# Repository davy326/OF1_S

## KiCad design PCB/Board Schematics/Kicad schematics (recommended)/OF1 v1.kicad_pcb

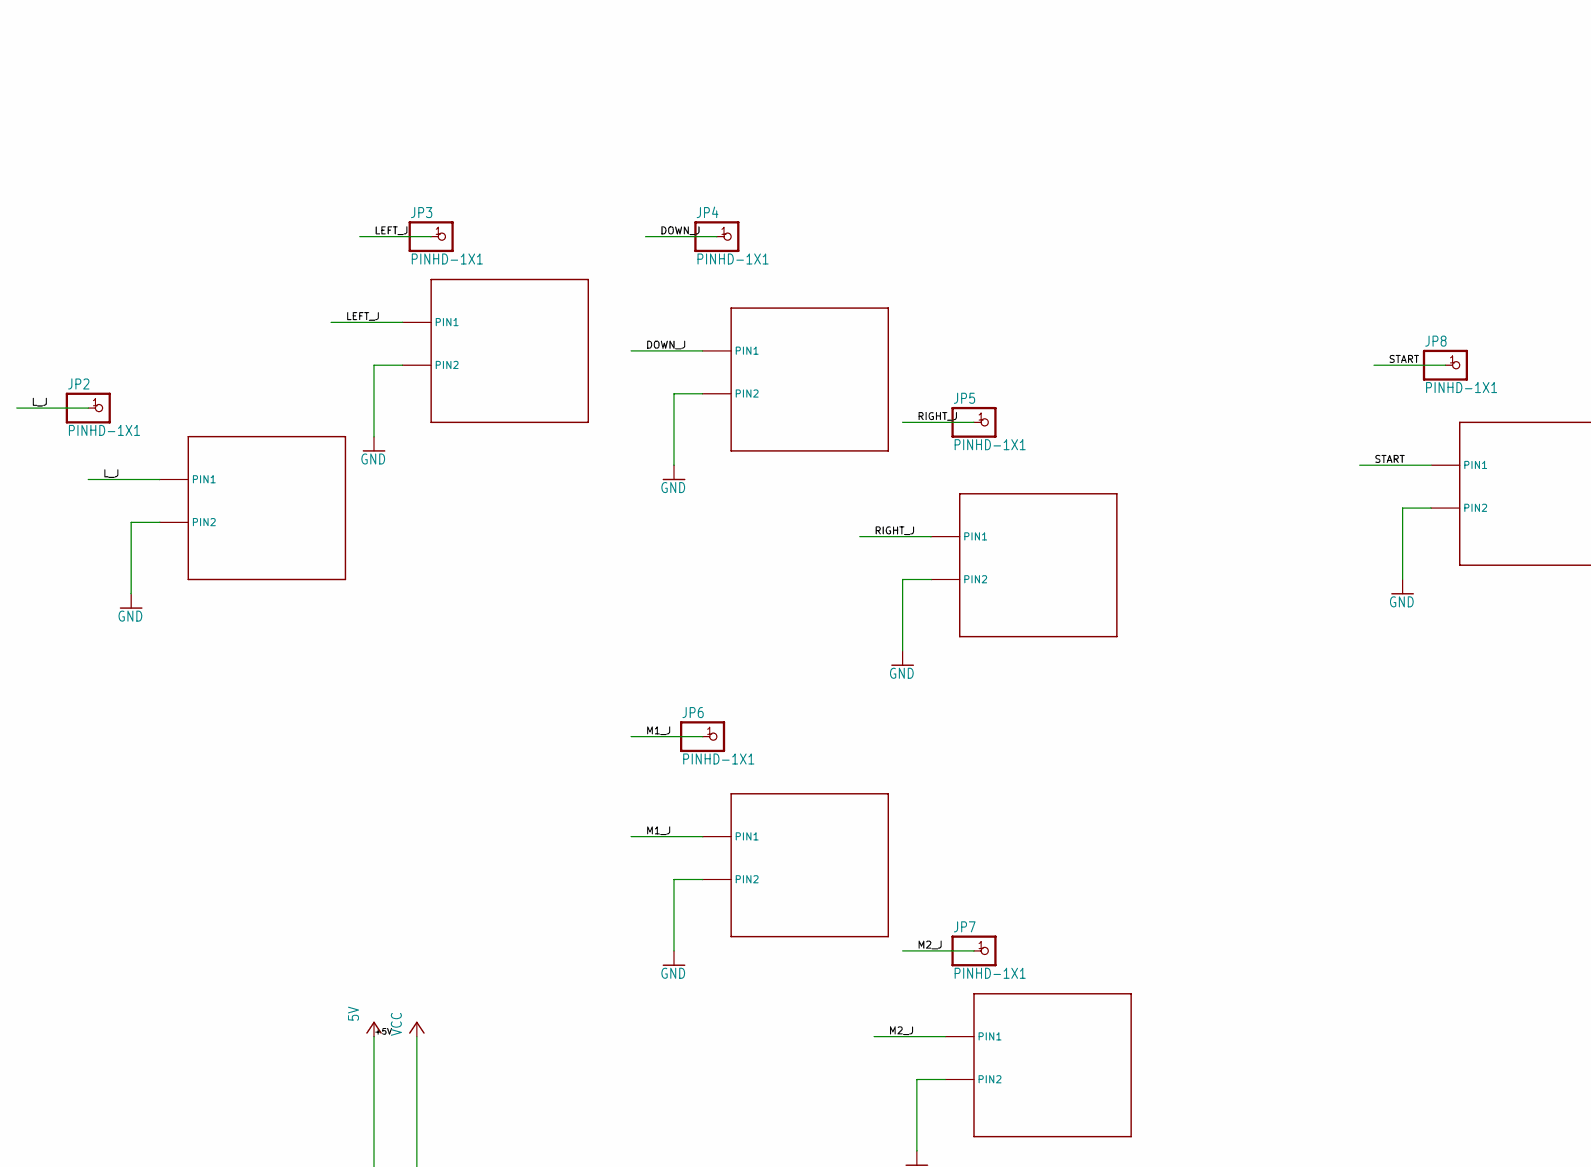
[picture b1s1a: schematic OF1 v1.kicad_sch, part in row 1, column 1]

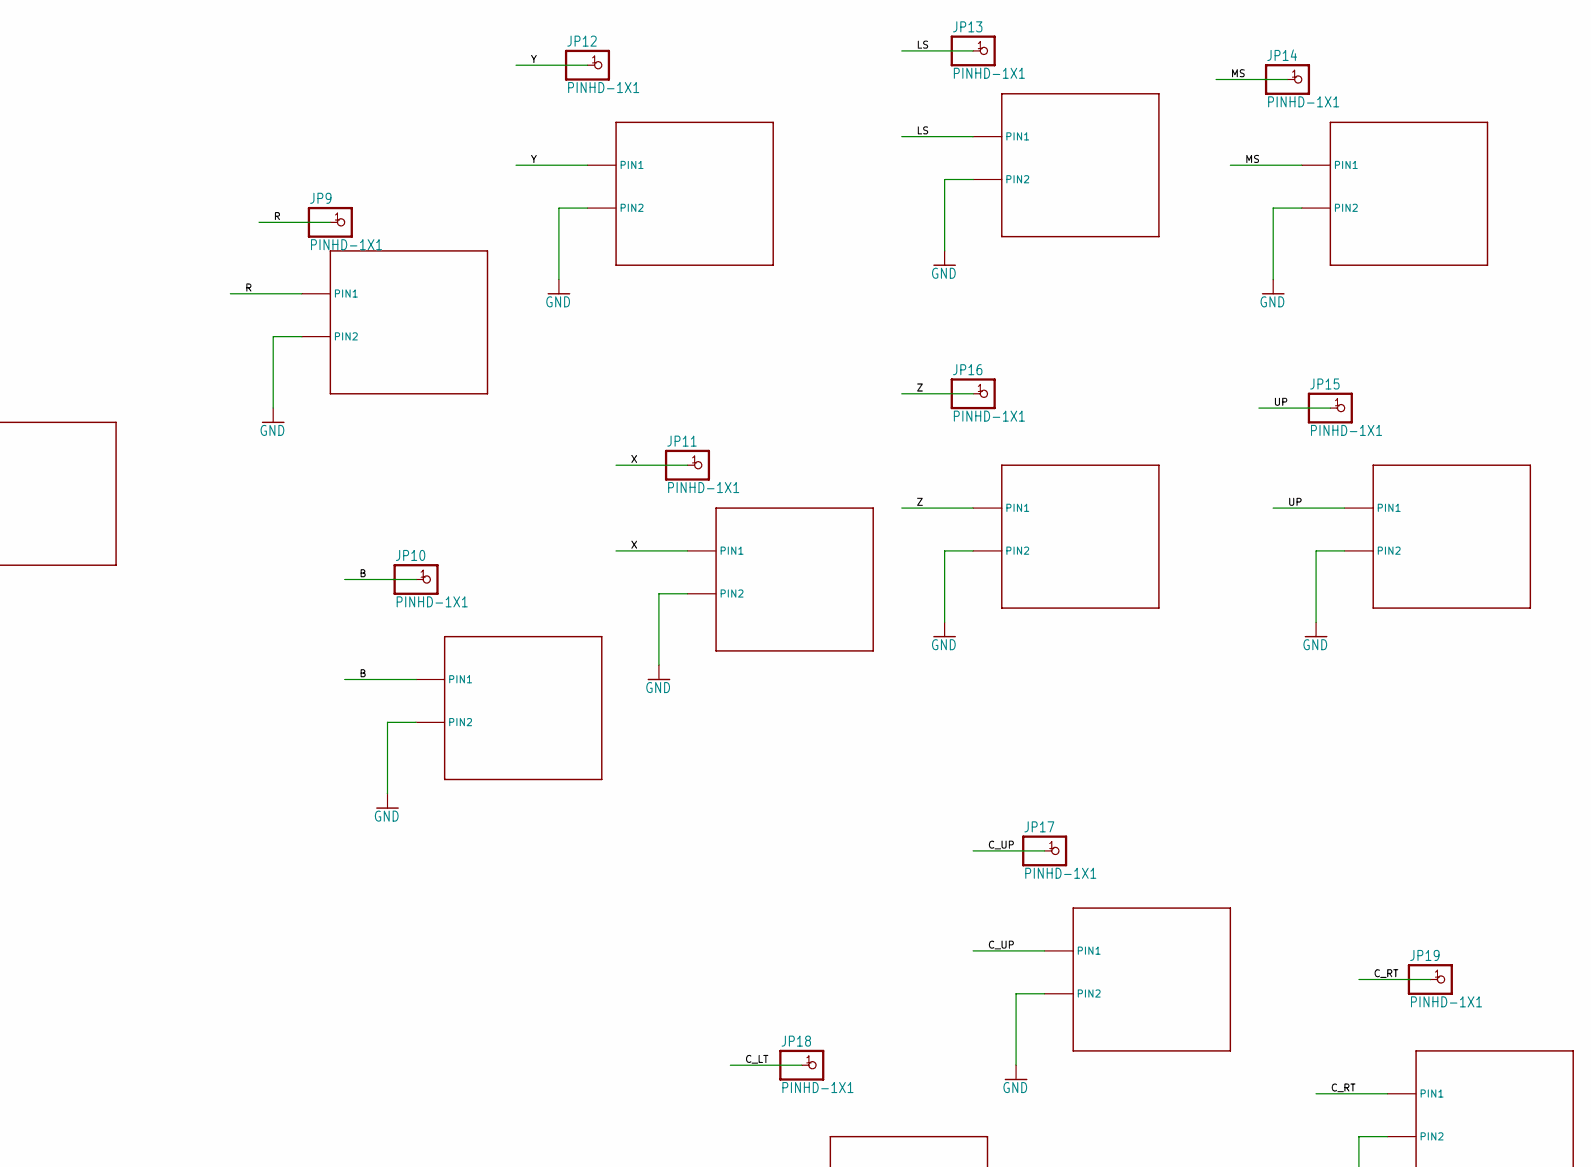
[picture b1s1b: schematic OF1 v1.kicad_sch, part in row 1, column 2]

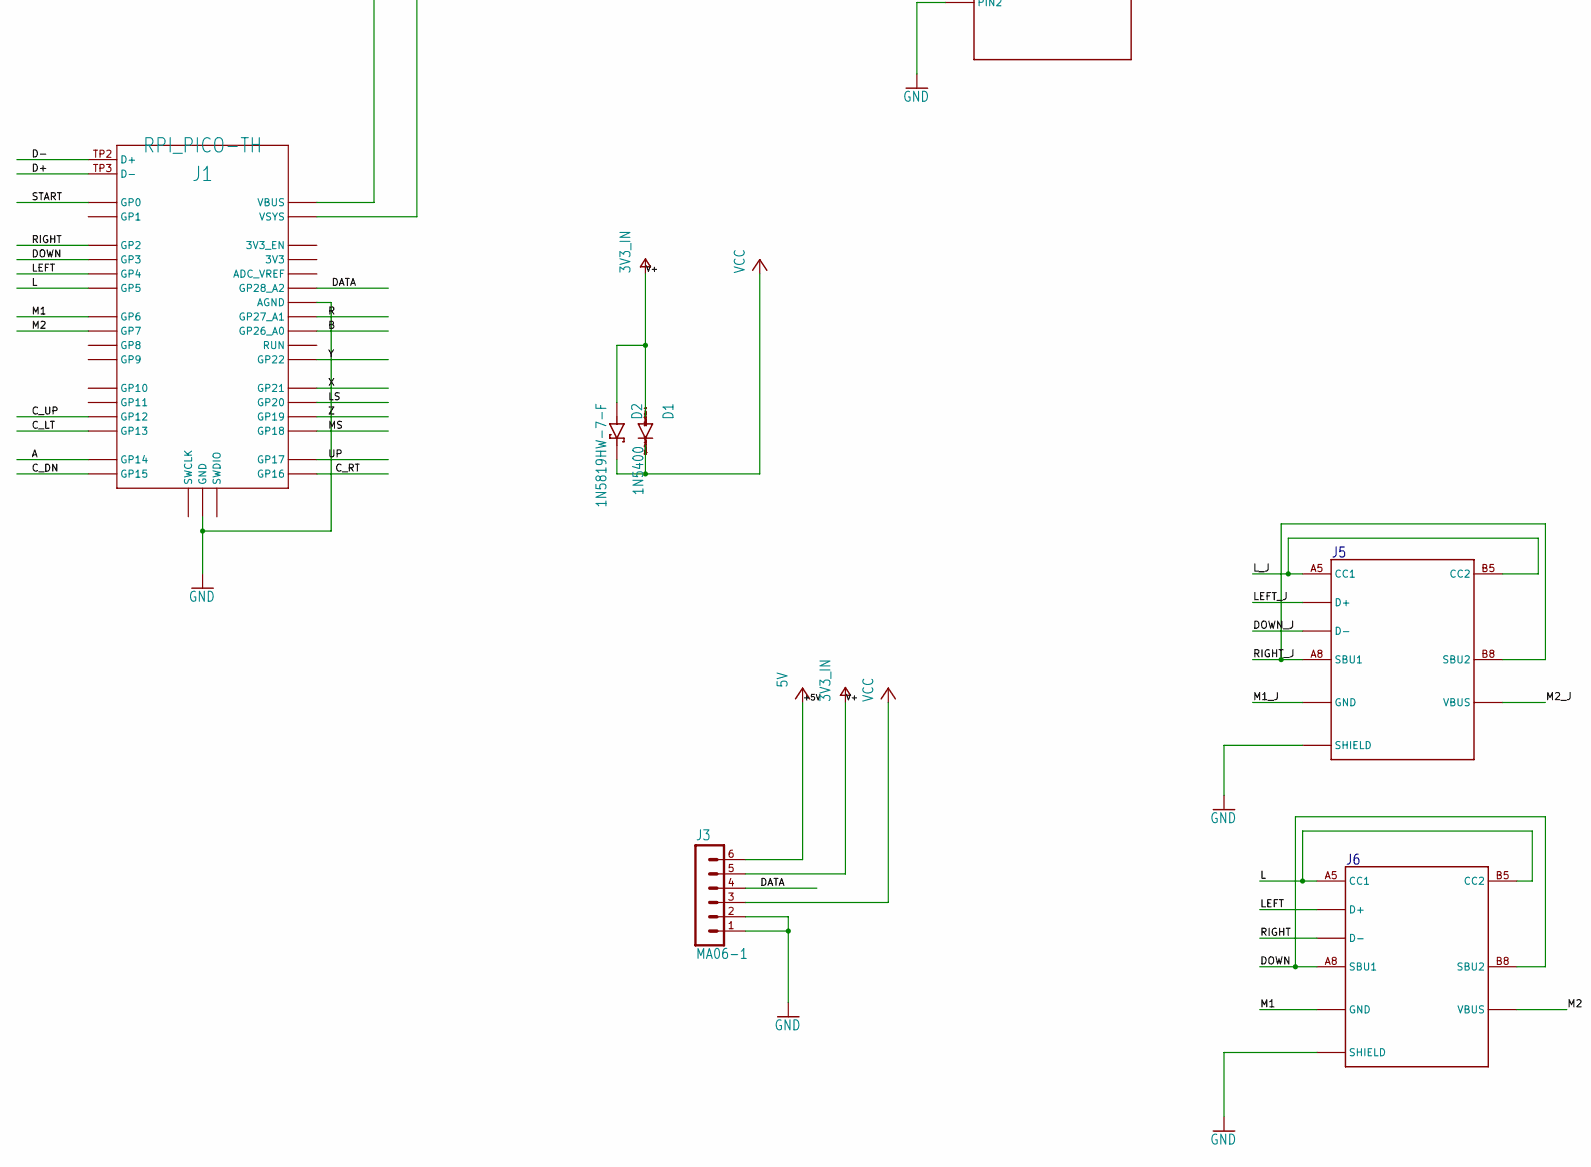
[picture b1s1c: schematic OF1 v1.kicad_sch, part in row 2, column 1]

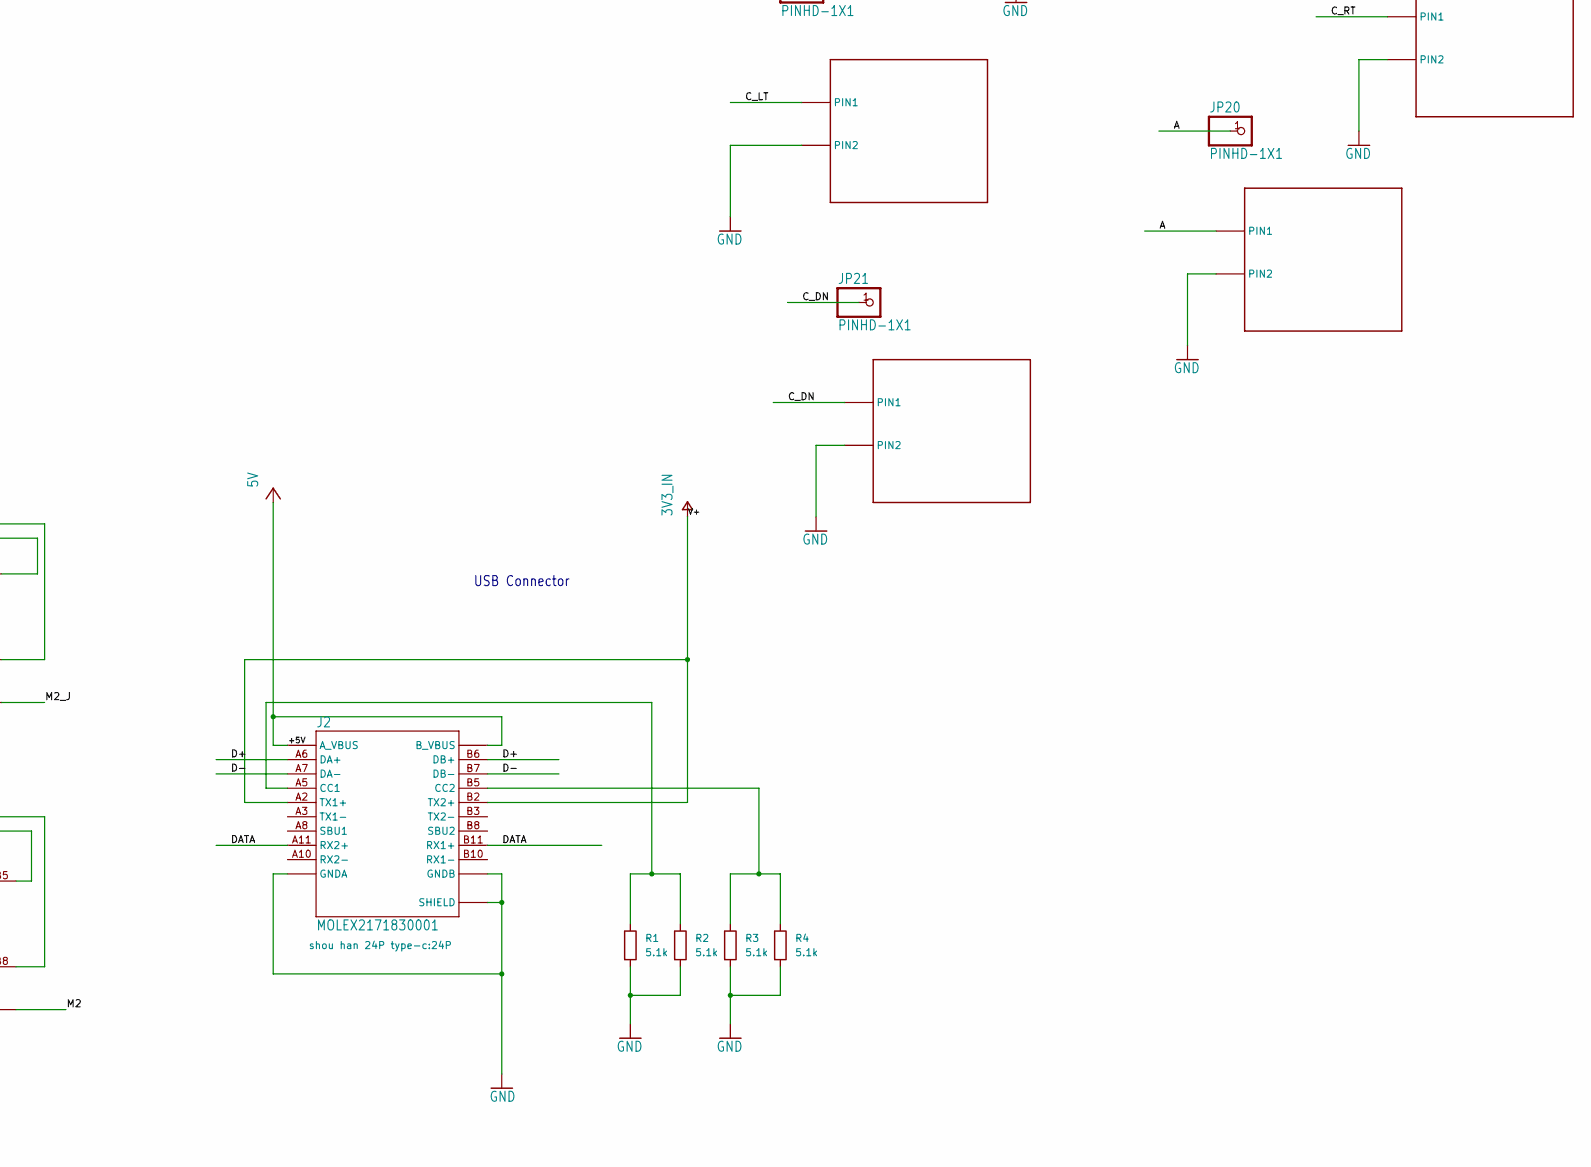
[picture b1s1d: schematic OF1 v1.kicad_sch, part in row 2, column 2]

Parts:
D1: 1N5400; DO201-15
D2: 1N5819HW-7-F; SOD3715X145N
J1: RPI_PICO-TH; RPI_PICO_TH
J2: MOLEX2171830001; 24P
J3: MA06-1
J4, J5: GT-USB-7010; 16P
JP2, JP3, JP4, JP5, JP6, JP7, JP8, JP9, JP10, JP11, JP12, JP13, JP14, JP15, JP16, JP17, JP18, JP19, JP20, JP21: PINHD-1X1; 1X01
R1, R3: 5.1k; R_Axial_DIN0207_L6.3mm_D2.5mm_P7.62mm_Horizontal
R2, R4: 5.1k; R_0603_1608Metric
U$1, U$2, U$4, U$5, U$6, U$7, U$8, U$9, U$10, U$11, U$12, U$13, U$14, U$15, U$16, U$17, U$18, U$19, U$20, U$21: MX-B; MX-BOTH

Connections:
+5V: J1.VBUS, J2.A4 (A_VBUS), J2.A9 (A_VBUS), J2.B4 (B_VBUS), J2.B9 (B_VBUS), J3.6
/A: J1.GP14, JP20.1, U$20.P$2 (PIN1), U$20.P$3 (PIN1)
/B: J1.GP26_A0, JP10.1, U$13.P$2 (PIN1), U$13.P$3 (PIN1)
/C_DN: J1.GP15, JP21.1, U$21.P$2 (PIN1), U$21.P$3 (PIN1)
/C_LT: J1.GP13, JP18.1, U$18.P$2 (PIN1), U$18.P$3 (PIN1)
/C_RT: J1.GP16, JP19.1, U$19.P$2 (PIN1), U$19.P$3 (PIN1)
/C_UP: J1.GP12, JP17.1, U$17.P$2 (PIN1), U$17.P$3 (PIN1)
/D+: J1.TP3 (D-), J2.A6 (DA+), J2.B6 (DB+)
/D-: J1.TP2 (D+), J2.A7 (DA-), J2.B7 (DB-)
/DATA: J1.GP28_A2, J2.A11 (RX2+), J2.B11 (RX1+), J3.4
/DOWN: J1.GP3, J4.A8 (SBU1), J4.B8 (SBU2)
/DOWN_J: J5.A7 (D-), J5.B7 (D-), JP4.1, U$4.P$2 (PIN1), U$4.P$3 (PIN1)
/L: J1.GP5, J4.A5 (CC1), J4.B5 (CC2)
/LEFT: J1.GP4, J4.A6 (D+), J4.B6 (D+)
/LEFT_J: J5.A6 (D+), J5.B6 (D+), JP3.1, U$2.P$2 (PIN1), U$2.P$3 (PIN1)
/LS: J1.GP20, JP13.1, U$11.P$2 (PIN1), U$11.P$3 (PIN1)
/L_J: J5.A5 (CC1), J5.B5 (CC2), JP2.1, U$1.P$2 (PIN1), U$1.P$3 (PIN1)
/M1: J1.GP6, J4.A1/B12 (GND), J4.B1/A12 (GND)
/M1_J: J5.A1/B12 (GND), J5.B1/A12 (GND), JP6.1, U$6.P$2 (PIN1), U$6.P$3 (PIN1)
/M2: J1.GP7, J4.A4/B9 (VBUS), J4.B4/A9 (VBUS)
/M2_J: J5.A4/B9 (VBUS), J5.B4/A9 (VBUS), JP7.1, U$7.P$2 (PIN1), U$7.P$3 (PIN1)
/MS: J1.GP18, JP14.1, U$12.P$2 (PIN1), U$12.P$3 (PIN1)
/R: J1.GP27_A1, JP9.1, U$9.P$2 (PIN1), U$9.P$3 (PIN1)
/RIGHT: J1.GP2, J4.A7 (D-), J4.B7 (D-)
/RIGHT_J: J5.A8 (SBU1), J5.B8 (SBU2), JP5.1, U$5.P$2 (PIN1), U$5.P$3 (PIN1)
/START: J1.GP0, JP8.1, U$8.P$2 (PIN1), U$8.P$3 (PIN1)
/UP: J1.GP17, JP15.1, U$16.P$2 (PIN1), U$16.P$3 (PIN1)
/X: J1.GP21, JP11.1, U$14.P$2 (PIN1), U$14.P$3 (PIN1)
/Y: J1.GP22, JP12.1, U$10.P$2 (PIN1), U$10.P$3 (PIN1)
/Z: J1.GP19, JP16.1, U$15.P$2 (PIN1), U$15.P$3 (PIN1)
GND: J1.AGND, J1.GND@1 (GND), J1.GND@2 (GND), J1.GND@3 (GND), J1.GND@4 (GND), J1.GND@5 (GND), J1.GND@6 (GND), J1.GND@7 (GND), J1.GND@8 (GND), J2.A1 (GNDA), J2.A12 (GNDA), J2.B1 (GNDB), J2.B12 (GNDB), J2.SHIELD1 (SHIELD), J2.SHIELD2 (SHIELD), J2.SHIELD3 (SHIELD), J2.SHIELD4 (SHIELD), J3.1, J3.2, J4.SHIELD1 (SHIELD), J4.SHIELD2 (SHIELD), J4.SHIELD3 (SHIELD), J4.SHIELD4 (SHIELD), J5.SHIELD1 (SHIELD), J5.SHIELD2 (SHIELD), J5.SHIELD3 (SHIELD), J5.SHIELD4 (SHIELD), R1.2, R2.2, R3.2, R4.2, U$1.P$1 (PIN2), U$1.P$4 (PIN2), U$2.P$1 (PIN2), U$2.P$4 (PIN2), U$4.P$1 (PIN2), U$4.P$4 (PIN2), U$5.P$1 (PIN2), U$5.P$4 (PIN2), U$6.P$1 (PIN2), U$6.P$4 (PIN2), U$7.P$1 (PIN2), U$7.P$4 (PIN2), U$8.P$1 (PIN2), U$8.P$4 (PIN2), U$9.P$1 (PIN2), U$9.P$4 (PIN2), U$10.P$1 (PIN2), U$10.P$4 (PIN2), U$11.P$1 (PIN2), U$11.P$4 (PIN2), U$12.P$1 (PIN2), U$12.P$4 (PIN2), U$13.P$1 (PIN2), U$13.P$4 (PIN2), U$14.P$1 (PIN2), U$14.P$4 (PIN2), U$15.P$1 (PIN2), U$15.P$4 (PIN2), U$16.P$1 (PIN2), U$16.P$4 (PIN2), U$17.P$1 (PIN2), U$17.P$4 (PIN2), U$18.P$1 (PIN2), U$18.P$4 (PIN2), U$19.P$1 (PIN2), U$19.P$4 (PIN2), U$20.P$1 (PIN2), U$20.P$4 (PIN2), U$21.P$1 (PIN2), U$21.P$4 (PIN2)
unnamed: J2.A5 (CC1), R1.1, R2.1
unnamed: J2.B5 (CC2), R3.1, R4.1
V+: D1.A, D2.A, J2.A2 (TX1+), J2.B2 (TX2+), J3.5
VCC: D1.C, D2.C (K), J1.VSYS, J3.3

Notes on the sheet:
USB Connector

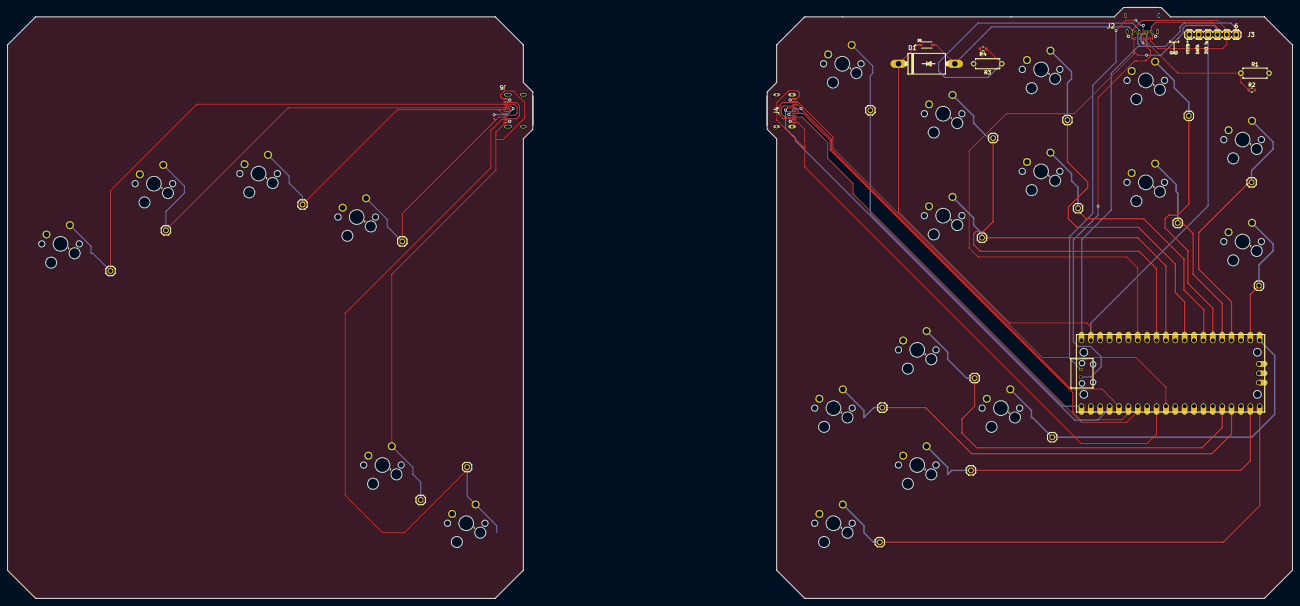
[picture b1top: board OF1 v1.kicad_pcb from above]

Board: 2 copper layers, 348.0 x 160.0 mm, 51 parts (0 on the bottom side), 35 nets.
